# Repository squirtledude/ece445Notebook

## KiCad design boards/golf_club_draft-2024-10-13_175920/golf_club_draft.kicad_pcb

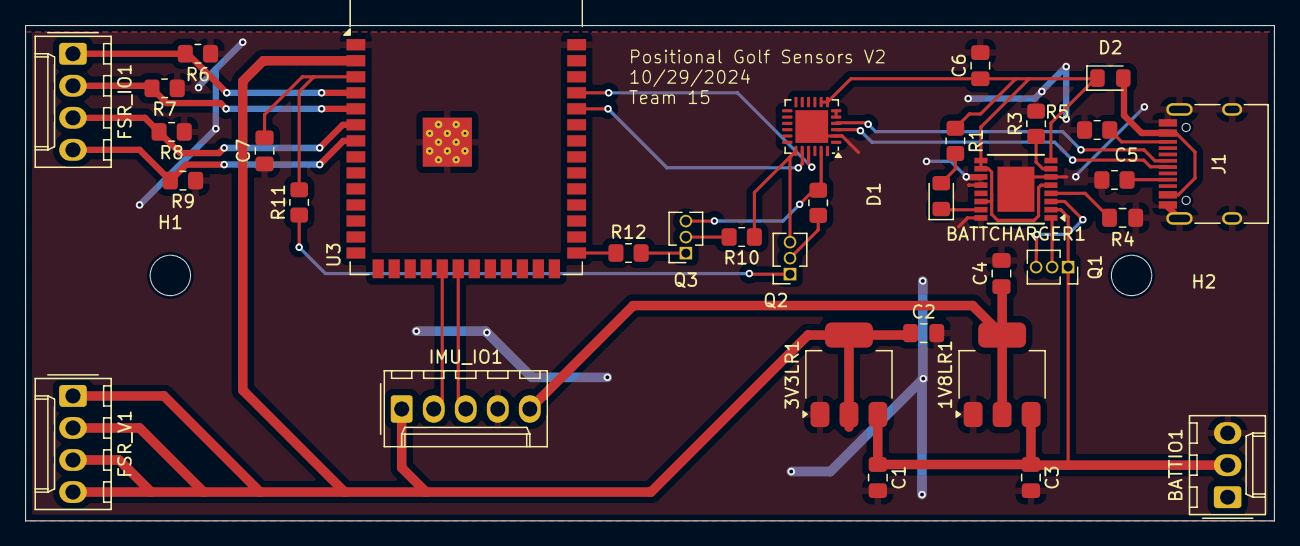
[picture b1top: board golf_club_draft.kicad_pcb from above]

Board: 2 copper layers, 99.0 x 39.3 mm, 36 parts (0 on the bottom side), 33 nets.

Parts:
1V8LR1: AZ1117-1.8; SOT-223-3_TabPin2
3V3LR1: AZ1117-3.3; SOT-223-3_TabPin2
BATTCHARGER1: LTC4060EFE; TSSOP-16-1EP_4.4x5mm_P0.65mm
BATTIO1: Conn_01x03_Socket; Molex_KK-254_AE-6410-03A_1x03_P2.54mm_Vertical
C1, C3: 10uF; C_0805_2012Metric_Pad1.18x1.45mm_HandSolder
C2, C4: 22uF; C_0805_2012Metric_Pad1.18x1.45mm_HandSolder
C5: 1.5nF; C_0805_2012Metric_Pad1.18x1.45mm_HandSolder
C6: 0.1uF; C_0805_2012Metric_Pad1.18x1.45mm_HandSolder
C7: 1uF; C_0805_2012Metric_Pad1.18x1.45mm_HandSolder
D1: LED; LED_0805_2012Metric_Pad1.15x1.40mm_HandSolder
D2: D_Schottky; D_0805_2012Metric_Pad1.15x1.40mm_HandSolder
FSR_IO1: Conn_01x04_Socket; Molex_KK-254_AE-6410-04A_1x04_P2.54mm_Vertical
FSR_V1: Conn_01x04_Socket; Molex_KK-254_AE-6410-04A_1x04_P2.54mm_Vertical
H1, H2: MountingHole; MountingHole_3.2mm_M3
IMU_IO1: Conn_01x05_Socket; Molex_KK-254_AE-6410-05A_1x05_P2.54mm_Vertical
J1: USB_C_Receptacle_USB2.0_16P; USB_C_Receptacle_HRO_TYPE-C-31-M-12
Q1, Q3: PNP; PinSocket_1x03_P1.27mm_Vertical
Q2: NPN; PinSocket_1x03_P1.27mm_Vertical
R1: 330; R_0805_2012Metric_Pad1.20x1.40mm_HandSolder
R2, R6, R7, R8, R9, R10, R11, R12: 10K; R_0805_2012Metric_Pad1.20x1.40mm_HandSolder
R3: 698; R_0805_2012Metric_Pad1.20x1.40mm_HandSolder
R4, R5: 5.1k; R_0805_2012Metric_Pad1.20x1.40mm_HandSolder
U2: CP2104; QFN-24-1EP_4x4mm_P0.5mm_EP2.6x2.6mm
U3: ESP32-S3-WROOM-1

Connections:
/1V8: 1V8LR1.2 (VO), C4.1, IMU_IO1.5
/3V3: 3V3LR1.2 (VO), C2.1, FSR_V1.1, FSR_V1.2, FSR_V1.3, FSR_V1.4, IMU_IO1.1, U3.2 (3V3)
/D+: J1.A6 (D+), U2.3 (D+)
/D-: J1.A7 (D-), U2.4 (D-)
/DTR: Q3.3 (E), R2.1, U2.23 (~DTR)
/FSR1: FSR_IO1.1, R6.2, U3.4 (IO4)
/FSR2: FSR_IO1.2, R7.2, U3.5 (IO5)
/FSR3: FSR_IO1.3, R8.2, U3.6 (IO6)
/FSR4: FSR_IO1.4, R9.2, U3.7 (IO7)
/GPIO0: R12.1, U3.27 (IO0)
/RESET: C7.2, R11.2, U3.3 (EN)
/RTS: Q2.3 (E), R10.1, U2.19 (~RTS)
/RXD: U2.20 (RXD), U3.36 (RXD0)
/SCL: IMU_IO1.3, U3.20 (IO12)
/SDA: IMU_IO1.2, U3.19 (IO11)
/TXD: U2.21 (TXD), U3.37 (TXD0)
/VBATT: 1V8LR1.3 (VI), 3V3LR1.3 (VI), BATTCHARGER1.2 (BAT), BATTIO1.2, C1.1, C3.1, Q1.1 (C)
/VIN: BATTCHARGER1.5 (~SHDN), BATTCHARGER1.8 (ARCT), BATTCHARGER1.9 (SEL0), BATTCHARGER1.10 (SEL1), BATTCHARGER1.14 (V_{CC}), C6.1, D2.1 (K), R1.1, U2.7 (REGIN), U2.8 (VBUS)
GND: 1V8LR1.1 (GND), 3V3LR1.1 (GND), BATTCHARGER1.6 (PAUSE), BATTCHARGER1.11 (NTC), BATTCHARGER1.12 (CHEM), BATTCHARGER1.16 (GND), BATTCHARGER1.17 (GNDPAD), BATTIO1.3, C1.2, C2.2, C3.2, C4.2, C5.2, C6.2, C7.1, IMU_IO1.4, J1.A1 (GND), J1.A12 (GND), J1.B1 (GND), J1.B12 (GND), J1.S1 (SHIELD), R3.2, R4.2, R5.2, R6.1, R7.1, R8.1, R9.1, U2.2 (GND), U2.25 (GND), U3.1 (GND), U3.40 (GND), U3.41 (GND)
unnamed: BATTCHARGER1.1 (DRIVE), Q1.2 (B)
unnamed: BATTCHARGER1.7 (PROG), R3.1
unnamed: BATTCHARGER1.3 (SENSE), Q1.3 (E)
unnamed: BATTCHARGER1.4 (TIMER), C5.1
unnamed: BATTCHARGER1.15 (~CHRG), D1.1 (K)
unnamed: D1.2 (A), R1.2
unnamed: D2.2 (A), J1.A4 (VBUS), J1.A9 (VBUS), J1.B4 (VBUS), J1.B9 (VBUS)
unnamed: J1.A5 (CC1), R4.1
unnamed: J1.B5 (CC2), R5.1
unnamed: Q2.2 (B), R2.2
unnamed: Q2.1 (C), R11.1
unnamed: Q3.2 (B), R10.2
unnamed: Q3.1 (C), R12.2
unnamed: U2.5 (VIO), U2.6 (VDD)

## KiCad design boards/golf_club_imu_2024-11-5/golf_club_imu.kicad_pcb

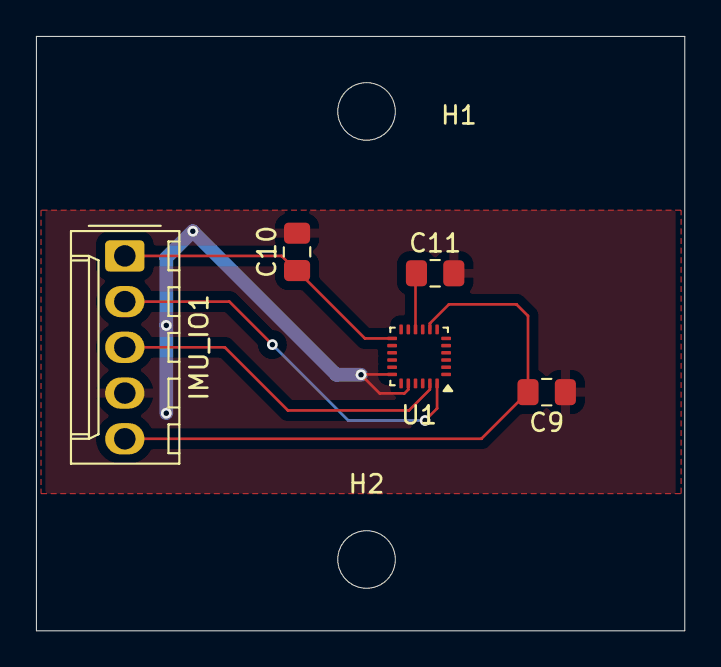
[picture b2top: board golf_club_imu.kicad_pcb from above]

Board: 2 copper layers, 36.0 x 33.0 mm, 7 parts (0 on the bottom side), 6 nets.

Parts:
C9, C10, C11: 0.1uF; C_0805_2012Metric_Pad1.18x1.45mm_HandSolder
H1, H2: MountingHole; MountingHole_3.2mm_M3
IMU_IO1: Conn_01x05_Socket; Molex_KK-254_AE-6410-05A_1x05_P2.54mm_Vertical
U1: ICM-20948; InvenSense_QFN-24_3x3mm_P0.4mm

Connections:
/1V8: C9.2, IMU_IO1.5, U1.8 (VDDIO)
/3V3: C10.1, IMU_IO1.1, U1.13 (VDD)
/SCL: IMU_IO1.3, U1.23 (SCL/SCLK)
/SDA: IMU_IO1.2, U1.24 (SDA/SDI)
GND: C9.1, C10.2, C11.2, IMU_IO1.4, U1.18 (GND), U1.20 (GND)
unnamed: C11.1, U1.10 (REGOUT)

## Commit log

2024-09-17 init commit for notebooks. directory structure is in place and readmes are created per group member
2024-09-17 added rough draft proposal
2024-09-17 change formatting
2024-10-08 Wrote linear regulators, BMS charging, and began programming circuit
2024-10-08 Continued programming circuit (Through USBC)
2024-10-13 Finalized first draft of schematic
2024-10-13 one more commit for final first draft of schematic
2024-10-19 Add files via upload
    Footprints added
2024-10-22 Completed first draft of PCB
2024-10-29 3rd round PCB order revisions
2024-11-13 Some more kicad files, round 3 and 4
2024-11-14 Initial commit
    Generated by create-expo-app 3.1.1.
2024-12-02 push all, nearly working
2024-12-06 Updated README with template
2024-12-07 First few parts of lab notebook
2024-12-07 Added dates for all lab notebook entries
2024-12-08 more lab notebook edits
2024-12-08 ryan lab notebook finalized
2024-12-13 update lab notebook
2024-12-13 added images
2024-12-13 git notebook images finalized
